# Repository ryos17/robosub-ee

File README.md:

# Stanford RoboSub — Electrical Repo

Electrical subsystem for the Stanford RoboSub AUV. It includes PCB designs (KiCad), firmware, Python tools, and research.

🌐 [stanfordrobosub.org](https://www.stanfordrobosub.org/)

## Repository layout

- **`platformio.ini`** — PlatformIO config for building/flashing the Teensy firmware. `src_dir` points at one sketch folder; change it to pick which firmware gets flashed (see comments in the file).
- **`gen1/`** — First hardware generation: PCBs only. Deprecated; the sub no longer exists.
- **`gen2/`** — Second (current) generation: PCBs and firmware for the audio and Teensy boards.
- **`gen3/`** — Third generation (in progress): ongoing designs of PCBs with Micro Breakout, Battery Boards, Power Distribution.
- **`imported_parts/`** — Shared KiCad libraries: symbols, footprints, 3D models, import script, and the JLC parts order log.
- **`misc/`** — Older and experimental material.
- **`research/`** — Research work (whisper-based intervehicle communication).

## Sub setup (Jetson Orin)

### Fix the system clock

The Jetson has no battery-backed RTC, so after being powered off its clock can be wrong. A wrong date breaks TLS, so Claude Code, `git`, `pip`, etc. fail to connect. Fix it by syncing over the internet:

```bash
timedatectl                      # check: "System clock synchronized" and the date
sudo timedatectl set-ntp true    # sync the time over the internet
sudo systemctl restart systemd-timesyncd
timedatectl                      # the date should now be correct
```

### Connect to eduroam (Stanford)

Replace `SUNETID` and the password with your own (Stanford eduroam uses PEAP / MSCHAPv2 with `sunetid@stanford.edu` as the identity):

```bash
nmcli connection add type wifi ifname wlP1p1s0 con-name eduroam ssid eduroam \
  wifi-sec.key-mgmt wpa-eap 802-1x.eap peap 802-1x.phase2-auth mschapv2 \
  802-1x.identity SUNETID@stanford.edu 802-1x.password 'YOUR_PASSWORD'
nmcli connection up eduroam
```

If an `eduroam` connection already exists, update it instead of adding a new one:

```bash
nmcli connection modify eduroam 802-1x.identity SUNETID@stanford.edu 802-1x.password 'YOUR_PASSWORD'
nmcli connection up eduroam
```

Don't commit your password. Afterwards, run the clock fix above if Claude still can't connect.

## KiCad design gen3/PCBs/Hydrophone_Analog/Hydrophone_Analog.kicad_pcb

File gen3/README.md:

# Gen 3 Submarine (in progress)

The third hardware generation, currently being designed. The proposed system
architecture is shown below; the boards under [`PCBs/`](PCBs/) are the work
toward it. The current working vehicle is still [`gen2/`](../gen2/).

## PCBs

- **`Micro_Breakout/`** — the main breakout board for gen 3, the successor to
  the gen 2 MLU breakout. References the shared parts library in
  [`../../imported_parts`](../../imported_parts).
- **`Battery_Boards/`** — the gen 3 power-management / battery boards, the
  follow-on to the gen 2 `Power_Management` boards (which had heat problems).
  Two design variants:
  - **`Power_ManagementV3_diode/`** — the diode-based design; this is the lead
    design.
  - **`Power_ManagementV3_eli/`** — Eli's alternative design, kept as a backup.
- **`Power_Distribution/`** — the gen 3 power-distribution board (battery →
  rails).
- **`to_order/`** — staging area for boards that are ready to be fabricated
  (currently empty).

## TODO

- Finalize how signals/power route in and out of `Micro_Breakout`, and choose
  the physical dimensions of all the boards.
- Order the PCBs.

_Last updated: 2026-07-20_

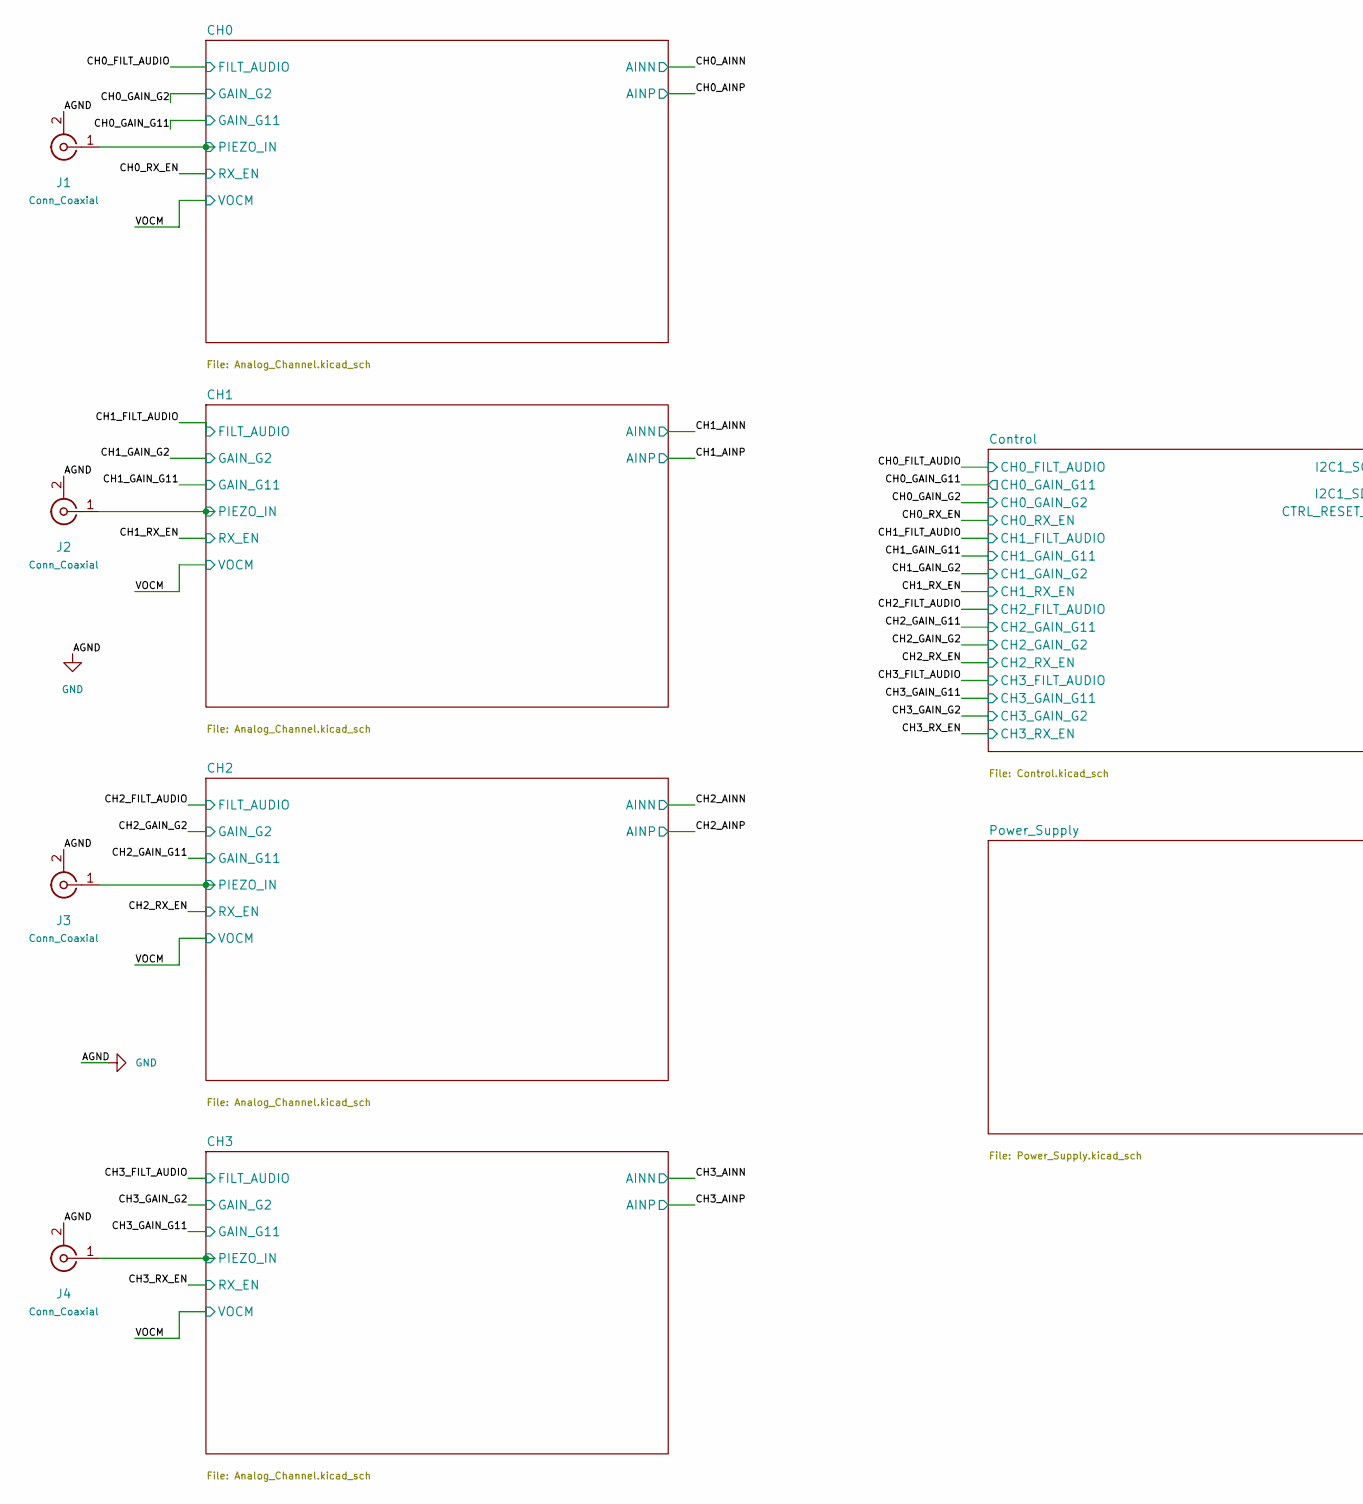
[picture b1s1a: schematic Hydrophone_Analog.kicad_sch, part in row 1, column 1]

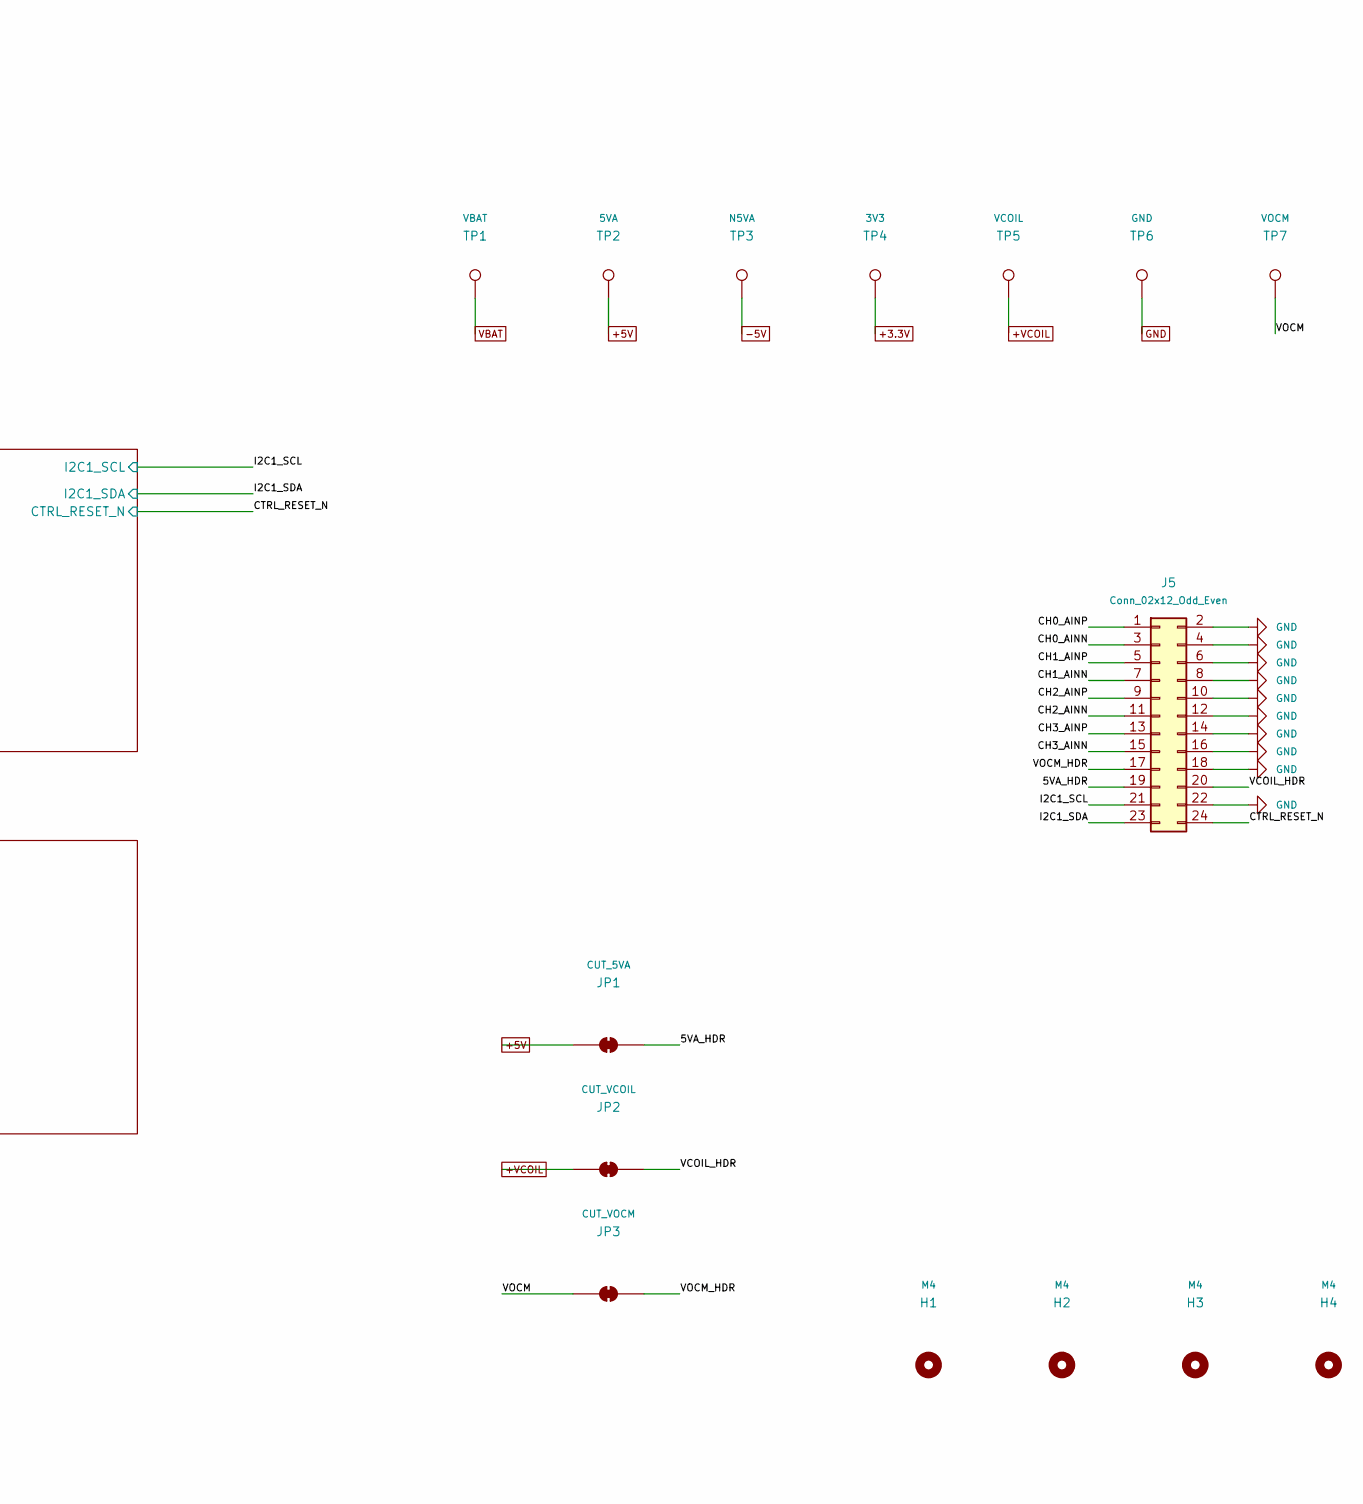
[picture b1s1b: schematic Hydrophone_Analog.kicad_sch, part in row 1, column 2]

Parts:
H1, H2, H3, H4: M4; MountingHole_4.3mm_M4
J1, J2, J3, J4: Conn_Coaxial; PinHeader_1x02_P2.54mm_Vertical
J5: Conn_02x12_Odd_Even; PinHeader_2x12_P2.54mm_Horizontal_BoardEdge
JP1: CUT_5VA; SolderJumper-2_P1.3mm_Bridged_RoundedPad1.0x1.5mm
JP2: CUT_VCOIL; SolderJumper-2_P1.3mm_Bridged_RoundedPad1.0x1.5mm
JP3: CUT_VOCM; SolderJumper-2_P1.3mm_Bridged_RoundedPad1.0x1.5mm
TP1: VBAT; TestPoint_Pad_D1.5mm
TP2: 5VA; TestPoint_Pad_D1.5mm
TP3: N5VA; TestPoint_Pad_D1.5mm
TP4: 3V3; TestPoint_Pad_D1.5mm
TP5: VCOIL; TestPoint_Pad_D1.5mm
TP6: GND; TestPoint_Pad_D1.5mm
TP7: VOCM; TestPoint_Pad_D1.5mm

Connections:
+3.3V: TP4.1; also elsewhere on the board
+5V: JP1.1 (A), TP2.1; also elsewhere on the board
+VCOIL: JP2.1 (A), TP5.1; also elsewhere on the board
-5V: TP3.1; also elsewhere on the board
/5VA_HDR: J5.19, JP1.2 (B)
/CH0/PIEZO_IN: J1.1 (In); also elsewhere on the board
/CH0_AINN: J5.3; also elsewhere on the board
/CH0_AINP: J5.1; also elsewhere on the board
/CH1/PIEZO_IN: J2.1 (In); also elsewhere on the board
/CH1_AINN: J5.7; also elsewhere on the board
/CH1_AINP: J5.5; also elsewhere on the board
/CH2/PIEZO_IN: J3.1 (In); also elsewhere on the board
/CH2_AINN: J5.11; also elsewhere on the board
/CH2_AINP: J5.9; also elsewhere on the board
/CH3/PIEZO_IN: J4.1 (In); also elsewhere on the board
/CH3_AINN: J5.15; also elsewhere on the board
/CH3_AINP: J5.13; also elsewhere on the board
/CTRL_RESET_N: J5.24; also elsewhere on the board
/I2C1_SCL: J5.21; also elsewhere on the board
/I2C1_SDA: J5.23; also elsewhere on the board
/VCOIL_HDR: J5.20, JP2.2 (B)
/VOCM: JP3.1 (A), TP7.1; also elsewhere on the board
/VOCM_HDR: J5.17, JP3.2 (B)
GND: J1.2 (Ext), J2.2 (Ext), J3.2 (Ext), J4.2 (Ext), J5.2, J5.4, J5.6, J5.8, J5.10, J5.12, J5.14, J5.16, J5.18, J5.22, TP6.1; also elsewhere on the board
VBAT: TP1.1; also elsewhere on the board

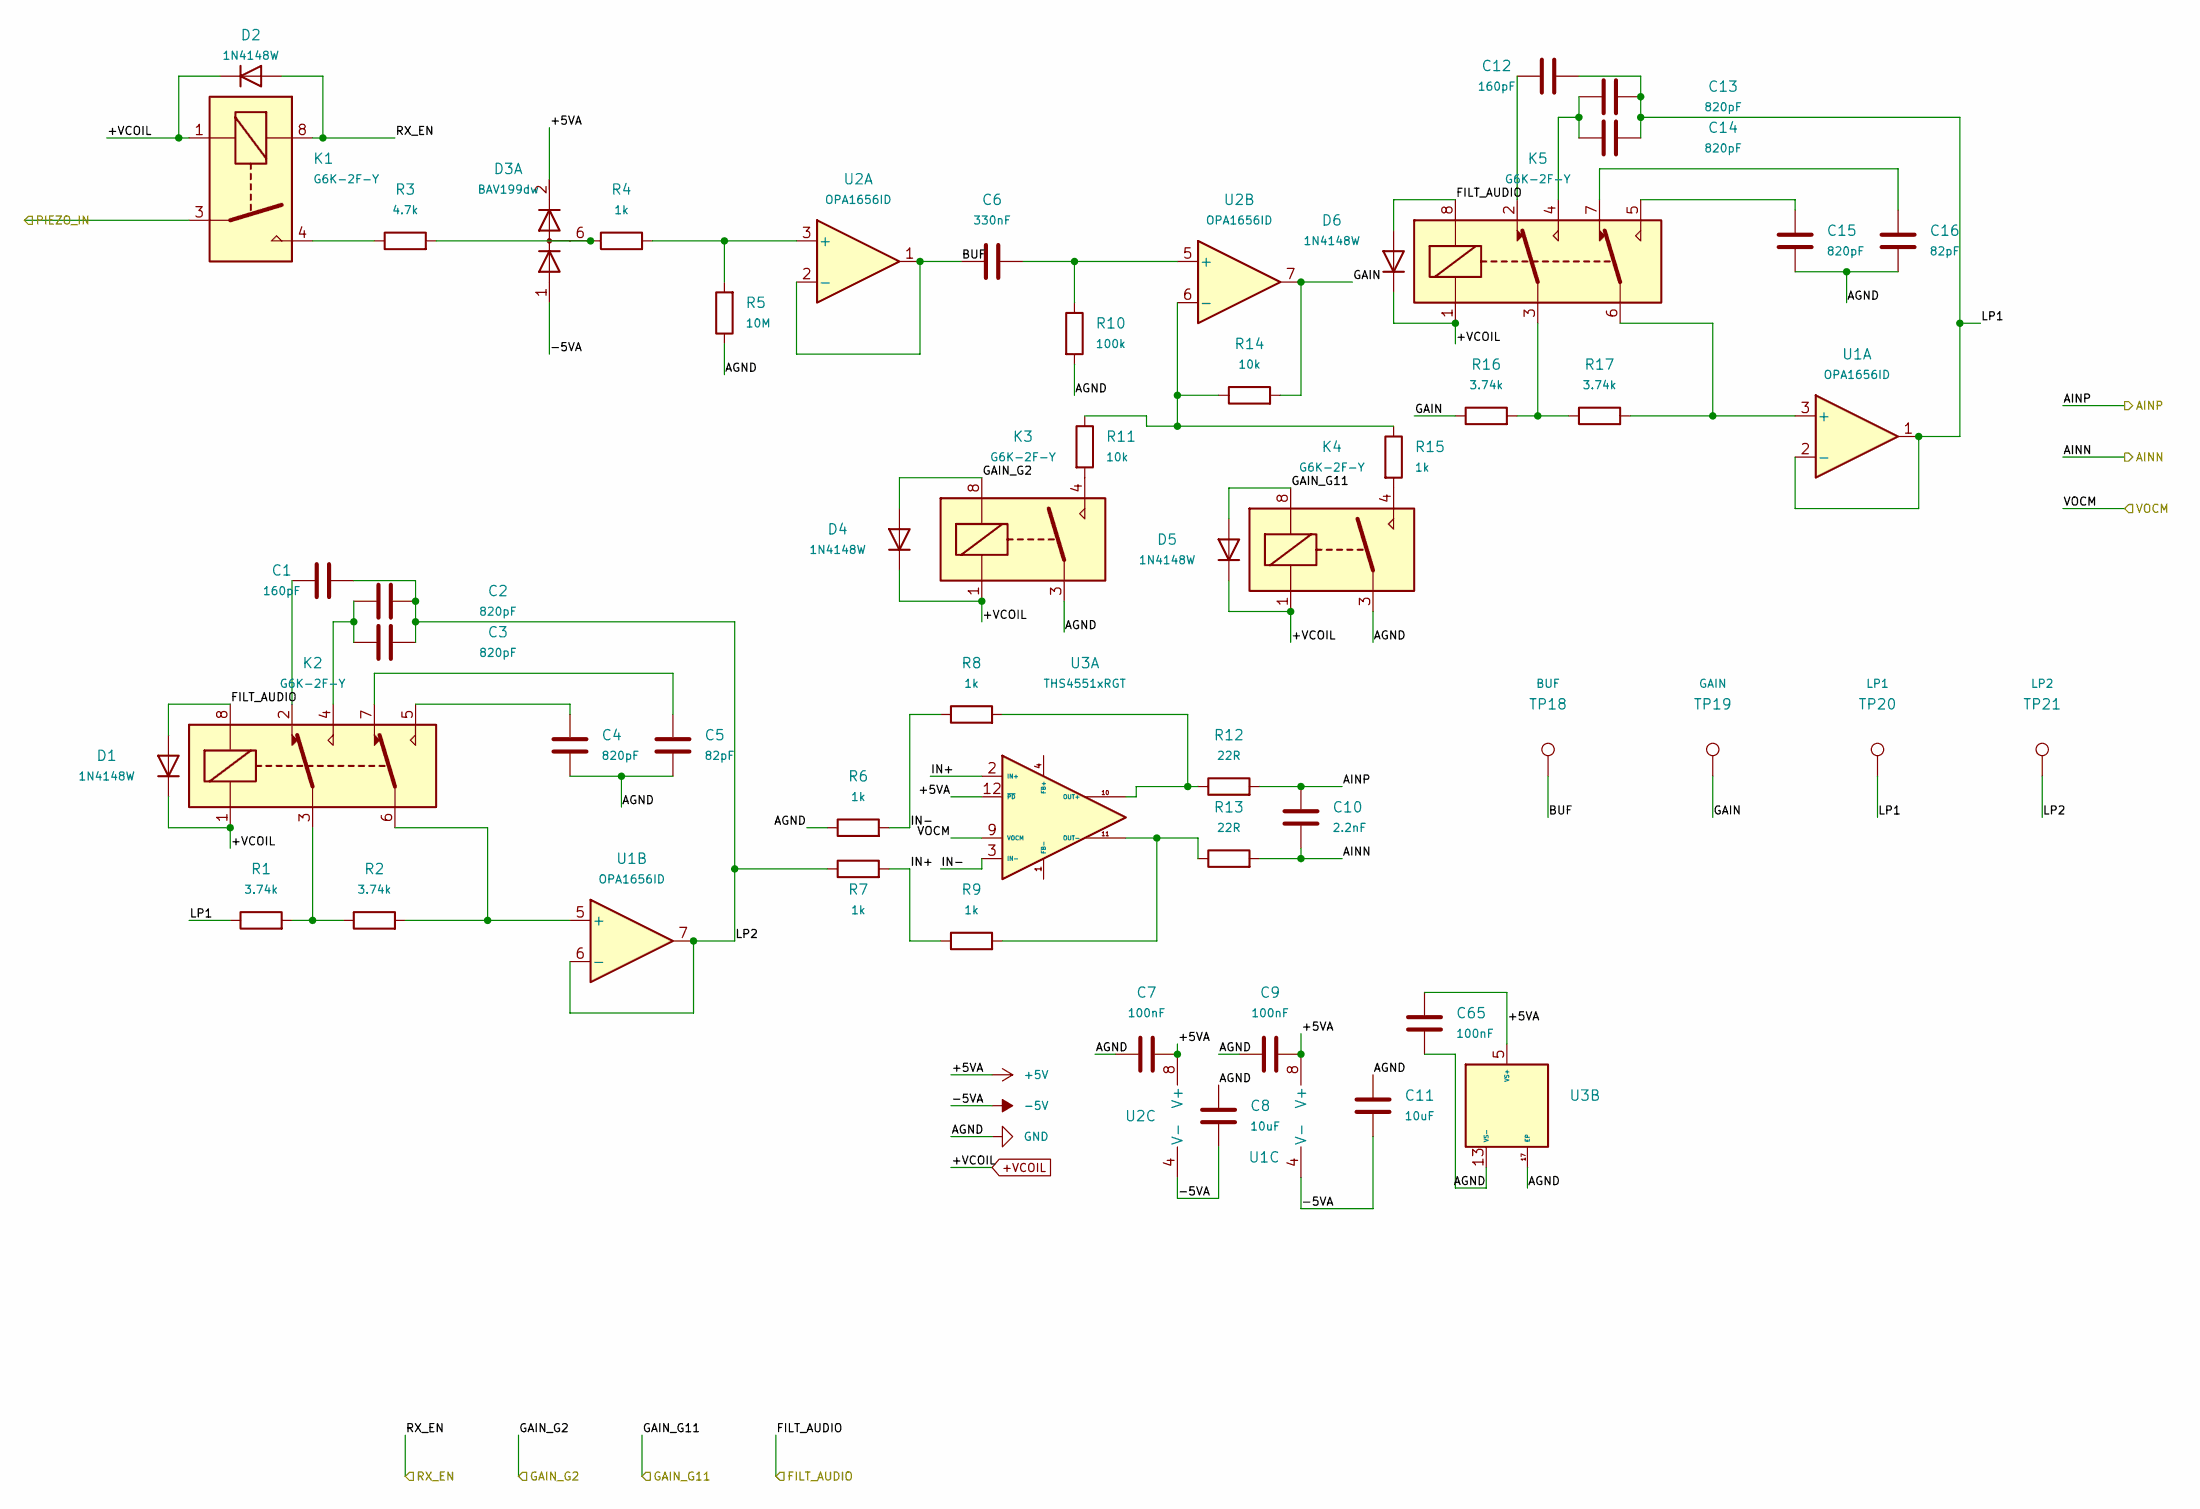
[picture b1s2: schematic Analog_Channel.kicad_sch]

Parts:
C1, C12: 160pF; C_0805_2012Metric
C2, C3, C4, C13, C14, C15: 820pF; C_0805_2012Metric
C5, C16: 82pF; C_0805_2012Metric
C6: 330nF; C_0805_2012Metric
C7, C9, C65: 100nF; C_0805_2012Metric
C8, C11: 10uF; C_1206_3216Metric
C10: 2.2nF; C_0805_2012Metric
D1, D2, D4, D5, D6: 1N4148W; D_SOD-123
D3: BAV199dw; SOT-363_SC-70-6
K1, K2, K3, K4, K5: G6K-2F-Y; Relay_DPDT_Omron_G6K-2F-Y
R1, R2, R16, R17: 3.74k; R_0805_2012Metric
R3: 4.7k; R_0805_2012Metric
R4, R6, R7, R8, R9, R15: 1k; R_0805_2012Metric
R5: 10M; R_0805_2012Metric
R10: 100k; R_0805_2012Metric
R11, R14: 10k; R_0805_2012Metric
R12, R13: 22R; R_0805_2012Metric
TP18: BUF; TestPoint_Pad_D1.0mm
TP19: GAIN; TestPoint_Pad_D1.0mm
TP20: LP1; TestPoint_Pad_D1.0mm
TP21: LP2; TestPoint_Pad_D1.0mm
U1, U2: OPA1656ID; SOIC-8_3.9x4.9mm_P1.27mm
U3: THS4551xRGT; VQFN-16-1EP_3x3mm_P0.5mm_EP1.68x1.68mm

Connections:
+5V: C7.2, C9.2, C65.2, D3.2 (K2), U1.8 (V+), U2.8 (V+), U3.5 (VS+), U3.6 (VS+), U3.7 (VS+), U3.8 (VS+), U3.12 (~PD); also elsewhere on the board
+VCOIL: D1.1 (K), D2.1 (K), D4.1 (K), D5.1 (K), D6.1 (K), K1.1 (A2), K2.1 (A2), K3.1 (A2), K4.1 (A2), K5.1 (A2); also elsewhere on the board
-5V: C8.2, C11.2, D3.1 (A1), U1.4 (V-), U2.4 (V-); also elsewhere on the board
/CH0/BUF: C6.1, TP18.1, U2.1, U2.2 (-)
/CH0/GAIN: R14.2, R16.1, TP19.1, U2.7
/CH0/IN+: R7.2, R9.1, U3.2 (IN+)
/CH0/IN-: R6.2, R8.1, U3.3 (IN-)
/CH0/LP1: C12.2, C13.2, C14.2, R1.1, TP20.1, U1.1, U1.2 (-)
/CH0/LP2: C1.2, C2.2, C3.2, R7.1, TP21.1, U1.6 (-), U1.7
/CH0/PIEZO_IN: K1.3 (13); also elsewhere on the board
/CH0_AINN: C10.2, R13.2; also elsewhere on the board
/CH0_AINP: C10.1, R12.2; also elsewhere on the board
/CH0_FILT_AUDIO: D1.2 (A), D6.2 (A), K2.8 (A1), K5.8 (A1); also elsewhere on the board
/CH0_GAIN_G2: D4.2 (A), K3.8 (A1); also elsewhere on the board
/CH0_GAIN_G11: D5.2 (A), K4.8 (A1); also elsewhere on the board
/CH0_RX_EN: D2.2 (A), K1.8 (A1); also elsewhere on the board
/VOCM: U3.9 (VOCM); also elsewhere on the board
GND: C4.2, C5.2, C7.1, C8.1, C9.1, C11.1, C15.2, C16.2, C65.1, K3.3 (13), K4.3 (13), R5.1, R6.1, R10.2, U3.13 (VS-), U3.14 (VS-), U3.15 (VS-), U3.16 (VS-), U3.17 (EP); also elsewhere on the board
unnamed: D3.6 (K3A4), R3.2, R4.1
unnamed: K1.4 (14), R3.1
unnamed: K2.3 (11), R1.2, R2.1
unnamed: C1.1, K2.2 (12)
unnamed: C2.1, C3.1, K2.4 (14)
unnamed: K2.6 (21), R2.2, U1.5 (+)
unnamed: C5.1, K2.7 (22)
unnamed: C4.1, K2.5 (24)
unnamed: K3.4 (14), R11.2
unnamed: K4.4 (14), R15.2
unnamed: K5.3 (11), R16.2, R17.1
unnamed: C12.1, K5.2 (12)
unnamed: C13.1, C14.1, K5.4 (14)
unnamed: K5.6 (21), R17.2, U1.3 (+)
unnamed: C16.1, K5.7 (22)
unnamed: C15.1, K5.5 (24)
unnamed: R4.2, R5.2, U2.3 (+)
unnamed: C6.2, R10.1, U2.5 (+)
unnamed: R11.1, R14.1, R15.1, U2.6 (-)
unnamed: R8.2, R12.1, U3.10 (OUT+)
unnamed: R9.2, R13.1, U3.11 (OUT-)

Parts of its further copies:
C17, C28, C33, C44, C49, C60: 160pF; C_0805_2012Metric
C18, C19, C20, C29, C30, C31, C34, C35, C36, C45, C46, C47, C50, C51, C52, C61, C62, C63: 820pF; C_0805_2012Metric
C21, C32, C37, C48, C53, C64: 82pF; C_0805_2012Metric
C22, C38, C54: 330nF; C_0805_2012Metric
C23, C25, C39, C41, C55, C57, C66, C67, C68: 100nF; C_0805_2012Metric
C24, C27, C40, C43, C56, C59: 10uF; C_1206_3216Metric
C26, C42, C58: 2.2nF; C_0805_2012Metric
D7, D8, D10, D11, D12, D13, D14, D16, D17, D18, D19, D20, D22, D23, D24: 1N4148W; D_SOD-123
D9, D15, D21: BAV199dw; SOT-363_SC-70-6
K6, K7, K8, K9, K10, K11, K12, K13, K14, K15, K16, K17, K18, K19, K20: G6K-2F-Y; Relay_DPDT_Omron_G6K-2F-Y
R18, R19, R33, R34, R35, R36, R50, R51, R52, R53, R67, R68: 3.74k; R_0805_2012Metric
R20, R37, R54: 4.7k; R_0805_2012Metric
R21, R23, R24, R25, R26, R32, R38, R40, R41, R42, R43, R49, R55, R57, R58, R59, R60, R66: 1k; R_0805_2012Metric
R22, R39, R56: 10M; R_0805_2012Metric
R27, R44, R61: 100k; R_0805_2012Metric
R28, R31, R45, R48, R62, R65: 10k; R_0805_2012Metric
R29, R30, R46, R47, R63, R64: 22R; R_0805_2012Metric
TP10, TP14, TP22: BUF; TestPoint_Pad_D1.0mm
TP11, TP15, TP23: GAIN; TestPoint_Pad_D1.0mm
TP12, TP16, TP24: LP1; TestPoint_Pad_D1.0mm
TP13, TP17, TP25: LP2; TestPoint_Pad_D1.0mm
U4, U5, U10, U11, U16, U17: OPA1656ID; SOIC-8_3.9x4.9mm_P1.27mm
U6, U12, U18: THS4551xRGT; VQFN-16-1EP_3x3mm_P0.5mm_EP1.68x1.68mm

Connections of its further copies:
+5V: C23.2, C25.2, C39.2, C41.2, C55.2, C57.2, C66.2, C67.2, C68.2, D9.2 (K2), D15.2 (K2), D21.2 (K2), U4.8 (V+), U5.8 (V+), U6.5 (VS+), U6.6 (VS+), U6.7 (VS+), U6.8 (VS+), U6.12 (~PD), U10.8 (V+), U11.8 (V+), U12.5 (VS+), U12.6 (VS+), U12.7 (VS+), U12.8 (VS+), U12.12 (~PD), U16.8 (V+), U17.8 (V+), U18.5 (VS+), U18.6 (VS+), U18.7 (VS+), U18.8 (VS+), U18.12 (~PD); also elsewhere on the board
+VCOIL: D7.1 (K), D8.1 (K), D10.1 (K), D11.1 (K), D12.1 (K), D13.1 (K), D14.1 (K), D16.1 (K), D17.1 (K), D18.1 (K), D19.1 (K), D20.1 (K), D22.1 (K), D23.1 (K), D24.1 (K), K6.1 (A2), K7.1 (A2), K8.1 (A2), K9.1 (A2), K10.1 (A2), K11.1 (A2), K12.1 (A2), K13.1 (A2), K14.1 (A2), K15.1 (A2), K16.1 (A2), K17.1 (A2), K18.1 (A2), K19.1 (A2), K20.1 (A2); also elsewhere on the board
-5V: C24.2, C27.2, C40.2, C43.2, C56.2, C59.2, D9.1 (A1), D15.1 (A1), D21.1 (A1), U4.4 (V-), U5.4 (V-), U10.4 (V-), U11.4 (V-), U16.4 (V-), U17.4 (V-); also elsewhere on the board
/CH1/BUF: C22.1, TP10.1, U5.1, U5.2 (-)
/CH1/GAIN: R31.2, R33.1, TP11.1, U5.7
/CH1/IN+: R24.2, R26.1, U6.2 (IN+)
/CH1/IN-: R23.2, R25.1, U6.3 (IN-)
/CH1/LP1: C28.2, C29.2, C30.2, R18.1, TP12.1, U4.1, U4.2 (-)
/CH1/LP2: C17.2, C18.2, C19.2, R24.1, TP13.1, U4.6 (-), U4.7
/CH1/PIEZO_IN: K6.3 (13); also elsewhere on the board
/CH1_AINN: C26.2, R30.2; also elsewhere on the board
/CH1_AINP: C26.1, R29.2; also elsewhere on the board
/CH1_FILT_AUDIO: D7.2 (A), D12.2 (A), K7.8 (A1), K10.8 (A1); also elsewhere on the board
/CH1_GAIN_G2: D10.2 (A), K8.8 (A1); also elsewhere on the board
/CH1_GAIN_G11: D11.2 (A), K9.8 (A1); also elsewhere on the board
/CH1_RX_EN: D8.2 (A), K6.8 (A1); also elsewhere on the board
/CH2/BUF: C38.1, TP14.1, U10.1, U10.2 (-)
/CH2/GAIN: R48.2, R50.1, TP15.1, U10.7
/CH2/IN+: R41.2, R43.1, U12.2 (IN+)
/CH2/IN-: R40.2, R42.1, U12.3 (IN-)
/CH2/LP1: C44.2, C45.2, C46.2, R35.1, TP16.1, U11.1, U11.2 (-)
/CH2/LP2: C33.2, C34.2, C35.2, R41.1, TP17.1, U11.6 (-), U11.7
/CH2/PIEZO_IN: K11.3 (13); also elsewhere on the board
/CH2_AINN: C42.2, R47.2; also elsewhere on the board
/CH2_AINP: C42.1, R46.2; also elsewhere on the board
/CH2_FILT_AUDIO: D13.2 (A), D18.2 (A), K12.8 (A1), K15.8 (A1); also elsewhere on the board
/CH2_GAIN_G2: D16.2 (A), K13.8 (A1); also elsewhere on the board
/CH2_GAIN_G11: D17.2 (A), K14.8 (A1); also elsewhere on the board
/CH2_RX_EN: D14.2 (A), K11.8 (A1); also elsewhere on the board
/CH3/BUF: C54.1, TP22.1, U16.1, U16.2 (-)
/CH3/GAIN: R65.2, R67.1, TP23.1, U16.7
/CH3/IN+: R58.2, R60.1, U18.2 (IN+)
/CH3/IN-: R57.2, R59.1, U18.3 (IN-)
/CH3/LP1: C60.2, C61.2, C62.2, R52.1, TP24.1, U17.1, U17.2 (-)
/CH3/LP2: C49.2, C50.2, C51.2, R58.1, TP25.1, U17.6 (-), U17.7
/CH3/PIEZO_IN: K16.3 (13); also elsewhere on the board
/CH3_AINN: C58.2, R64.2; also elsewhere on the board
/CH3_AINP: C58.1, R63.2; also elsewhere on the board
/CH3_FILT_AUDIO: D19.2 (A), D24.2 (A), K17.8 (A1), K20.8 (A1); also elsewhere on the board
/CH3_GAIN_G2: D22.2 (A), K18.8 (A1); also elsewhere on the board
/CH3_GAIN_G11: D23.2 (A), K19.8 (A1); also elsewhere on the board
/CH3_RX_EN: D20.2 (A), K16.8 (A1); also elsewhere on the board
/VOCM: U6.9 (VOCM), U12.9 (VOCM), U18.9 (VOCM); also elsewhere on the board
GND: C20.2, C21.2, C23.1, C24.1, C25.1, C27.1, C31.2, C32.2, C36.2, C37.2, C39.1, C40.1, C41.1, C43.1, C47.2, C48.2, C52.2, C53.2, C55.1, C56.1, C57.1, C59.1, C63.2, C64.2, C66.1, C67.1, C68.1, K8.3 (13), K9.3 (13), K13.3 (13), K14.3 (13), K18.3 (13), K19.3 (13), R22.1, R23.1, R27.2, R39.1, R40.1, R44.2, R56.1, R57.1, R61.2, U6.13 (VS-), U6.14 (VS-), U6.15 (VS-), U6.16 (VS-), U6.17 (EP), U12.13 (VS-), U12.14 (VS-), U12.15 (VS-), U12.16 (VS-), U12.17 (EP), U18.13 (VS-), U18.14 (VS-), U18.15 (VS-), U18.16 (VS-), U18.17 (EP); also elsewhere on the board
unnamed: D9.6 (K3A4), R20.2, R21.1
unnamed: D15.6 (K3A4), R37.2, R38.1
unnamed: D21.6 (K3A4), R54.2, R55.1
unnamed: K6.4 (14), R20.1
unnamed: K7.3 (11), R18.2, R19.1
unnamed: C17.1, K7.2 (12)
unnamed: C18.1, C19.1, K7.4 (14)
unnamed: K7.6 (21), R19.2, U4.5 (+)
unnamed: C21.1, K7.7 (22)
unnamed: C20.1, K7.5 (24)
unnamed: K8.4 (14), R28.2
unnamed: K9.4 (14), R32.2
unnamed: K10.3 (11), R33.2, R34.1
unnamed: C28.1, K10.2 (12)
unnamed: C29.1, C30.1, K10.4 (14)
unnamed: K10.6 (21), R34.2, U4.3 (+)
unnamed: C32.1, K10.7 (22)
unnamed: C31.1, K10.5 (24)
unnamed: K11.4 (14), R37.1
unnamed: K12.3 (11), R35.2, R36.1
unnamed: C33.1, K12.2 (12)
unnamed: C34.1, C35.1, K12.4 (14)
unnamed: K12.6 (21), R36.2, U11.5 (+)
unnamed: C37.1, K12.7 (22)
unnamed: C36.1, K12.5 (24)
unnamed: K13.4 (14), R45.2
unnamed: K14.4 (14), R49.2
unnamed: K15.3 (11), R50.2, R51.1
unnamed: C44.1, K15.2 (12)
unnamed: C45.1, C46.1, K15.4 (14)
unnamed: K15.6 (21), R51.2, U11.3 (+)
unnamed: C48.1, K15.7 (22)
unnamed: C47.1, K15.5 (24)
unnamed: K16.4 (14), R54.1
unnamed: K17.3 (11), R52.2, R53.1
unnamed: C49.1, K17.2 (12)
unnamed: C50.1, C51.1, K17.4 (14)
unnamed: K17.6 (21), R53.2, U17.5 (+)
unnamed: C53.1, K17.7 (22)
unnamed: C52.1, K17.5 (24)
unnamed: K18.4 (14), R62.2
unnamed: K19.4 (14), R66.2
unnamed: K20.3 (11), R67.2, R68.1
unnamed: C60.1, K20.2 (12)
unnamed: C61.1, C62.1, K20.4 (14)
unnamed: K20.6 (21), R68.2, U17.3 (+)
unnamed: C64.1, K20.7 (22)
unnamed: C63.1, K20.5 (24)
unnamed: R21.2, R22.2, U5.3 (+)
unnamed: C22.2, R27.1, U5.5 (+)
unnamed: R28.1, R31.1, R32.1, U5.6 (-)
unnamed: R25.2, R29.1, U6.10 (OUT+)
unnamed: R26.2, R30.1, U6.11 (OUT-)
unnamed: R38.2, R39.2, U10.3 (+)
unnamed: C38.2, R44.1, U10.5 (+)
unnamed: R45.1, R48.1, R49.1, U10.6 (-)
unnamed: R42.2, R46.1, U12.10 (OUT+)
unnamed: R43.2, R47.1, U12.11 (OUT-)
unnamed: R55.2, R56.2, U16.3 (+)
unnamed: C54.2, R61.1, U16.5 (+)
unnamed: R62.1, R65.1, R66.1, U16.6 (-)
unnamed: R59.2, R63.1, U18.10 (OUT+)
unnamed: R60.2, R64.1, U18.11 (OUT-)

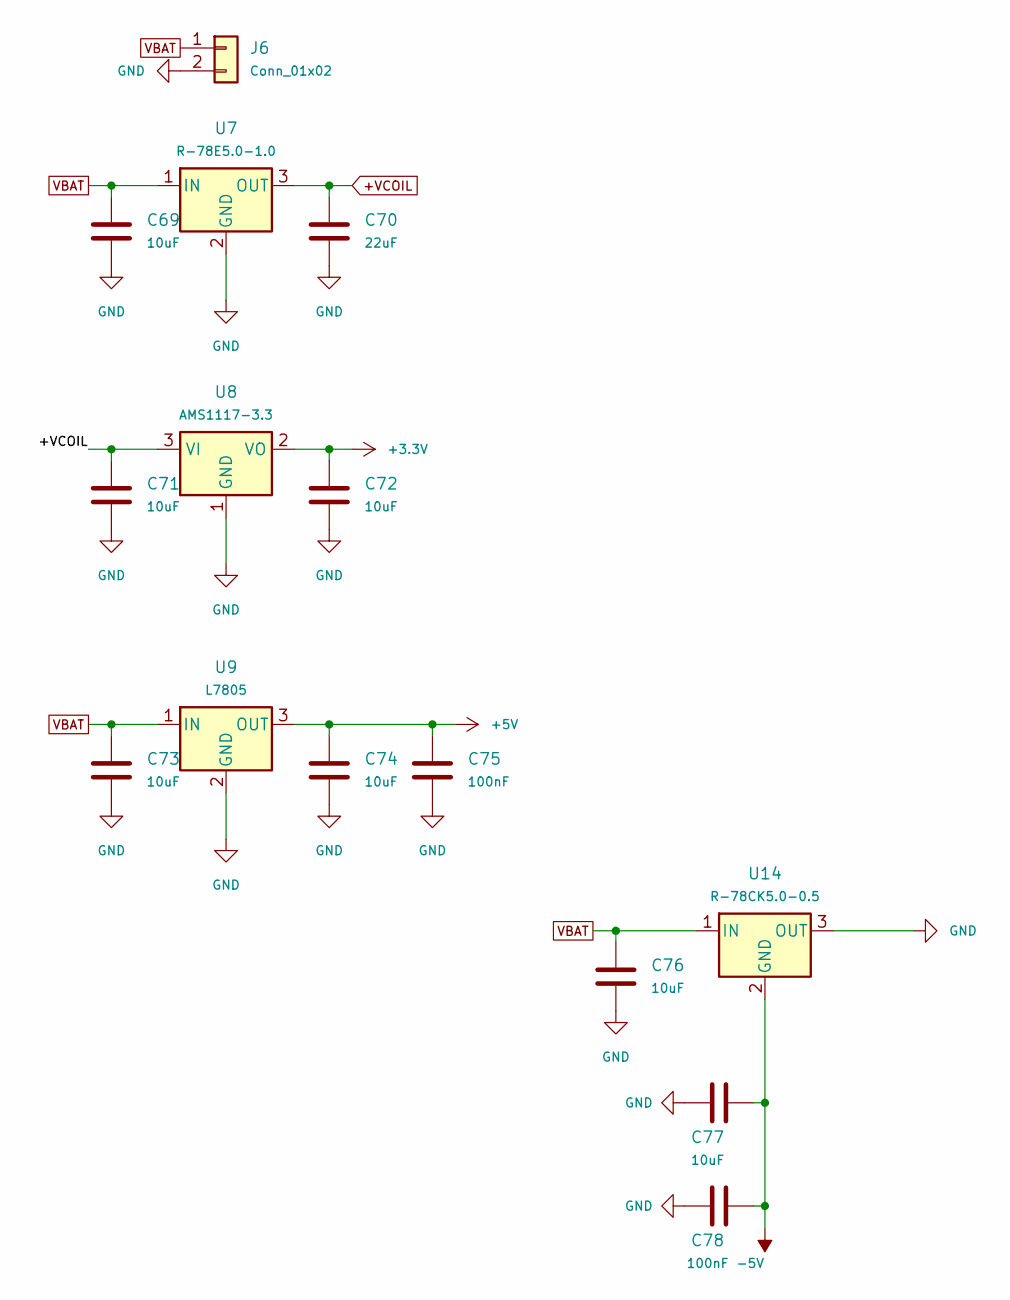
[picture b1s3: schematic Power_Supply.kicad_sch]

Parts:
C69, C71, C72, C73, C74, C76, C77: 10uF; C_1206_3216Metric
C70: 22uF; C_1206_3216Metric
C75, C78: 100nF; C_0805_2012Metric
J6: Conn_01x02; TerminalBlock_Phoenix_MKDS-1,5-2-5.08_1x02_P5.08mm_Horizont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
U7: R-78E5.0-1.0; Converter_DCDC_RECOM_R-78E-0.5_THT
U8: AMS1117-3.3; SOT-223-3_TabPin2
U9: L7805; TO-252-2
U14: R-78CK5.0-0.5; Converter_DCDC_RECOM_R-78E-0.5_THT

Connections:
+3.3V: C72.1, U8.2 (VO); also elsewhere on the board
+5V: C74.1, C75.1, U9.3 (OUT); also elsewhere on the board
+VCOIL: C70.1, C71.1, U7.3 (OUT), U8.3 (VI); also elsewhere on the board
-5V: C77.1, C78.1, U14.2 (GND); also elsewhere on the board
GND: C69.2, C70.2, C71.2, C72.2, C73.2, C74.2, C75.2, C76.2, C77.2, C78.2, J6.2, U7.2 (GND), U8.1 (GND), U9.2 (GND), U14.3 (OUT); also elsewhere on the board
VBAT: C69.1, C73.1, C76.1, J6.1, U7.1 (IN), U9.1 (IN), U14.1 (IN); also elsewhere on the board

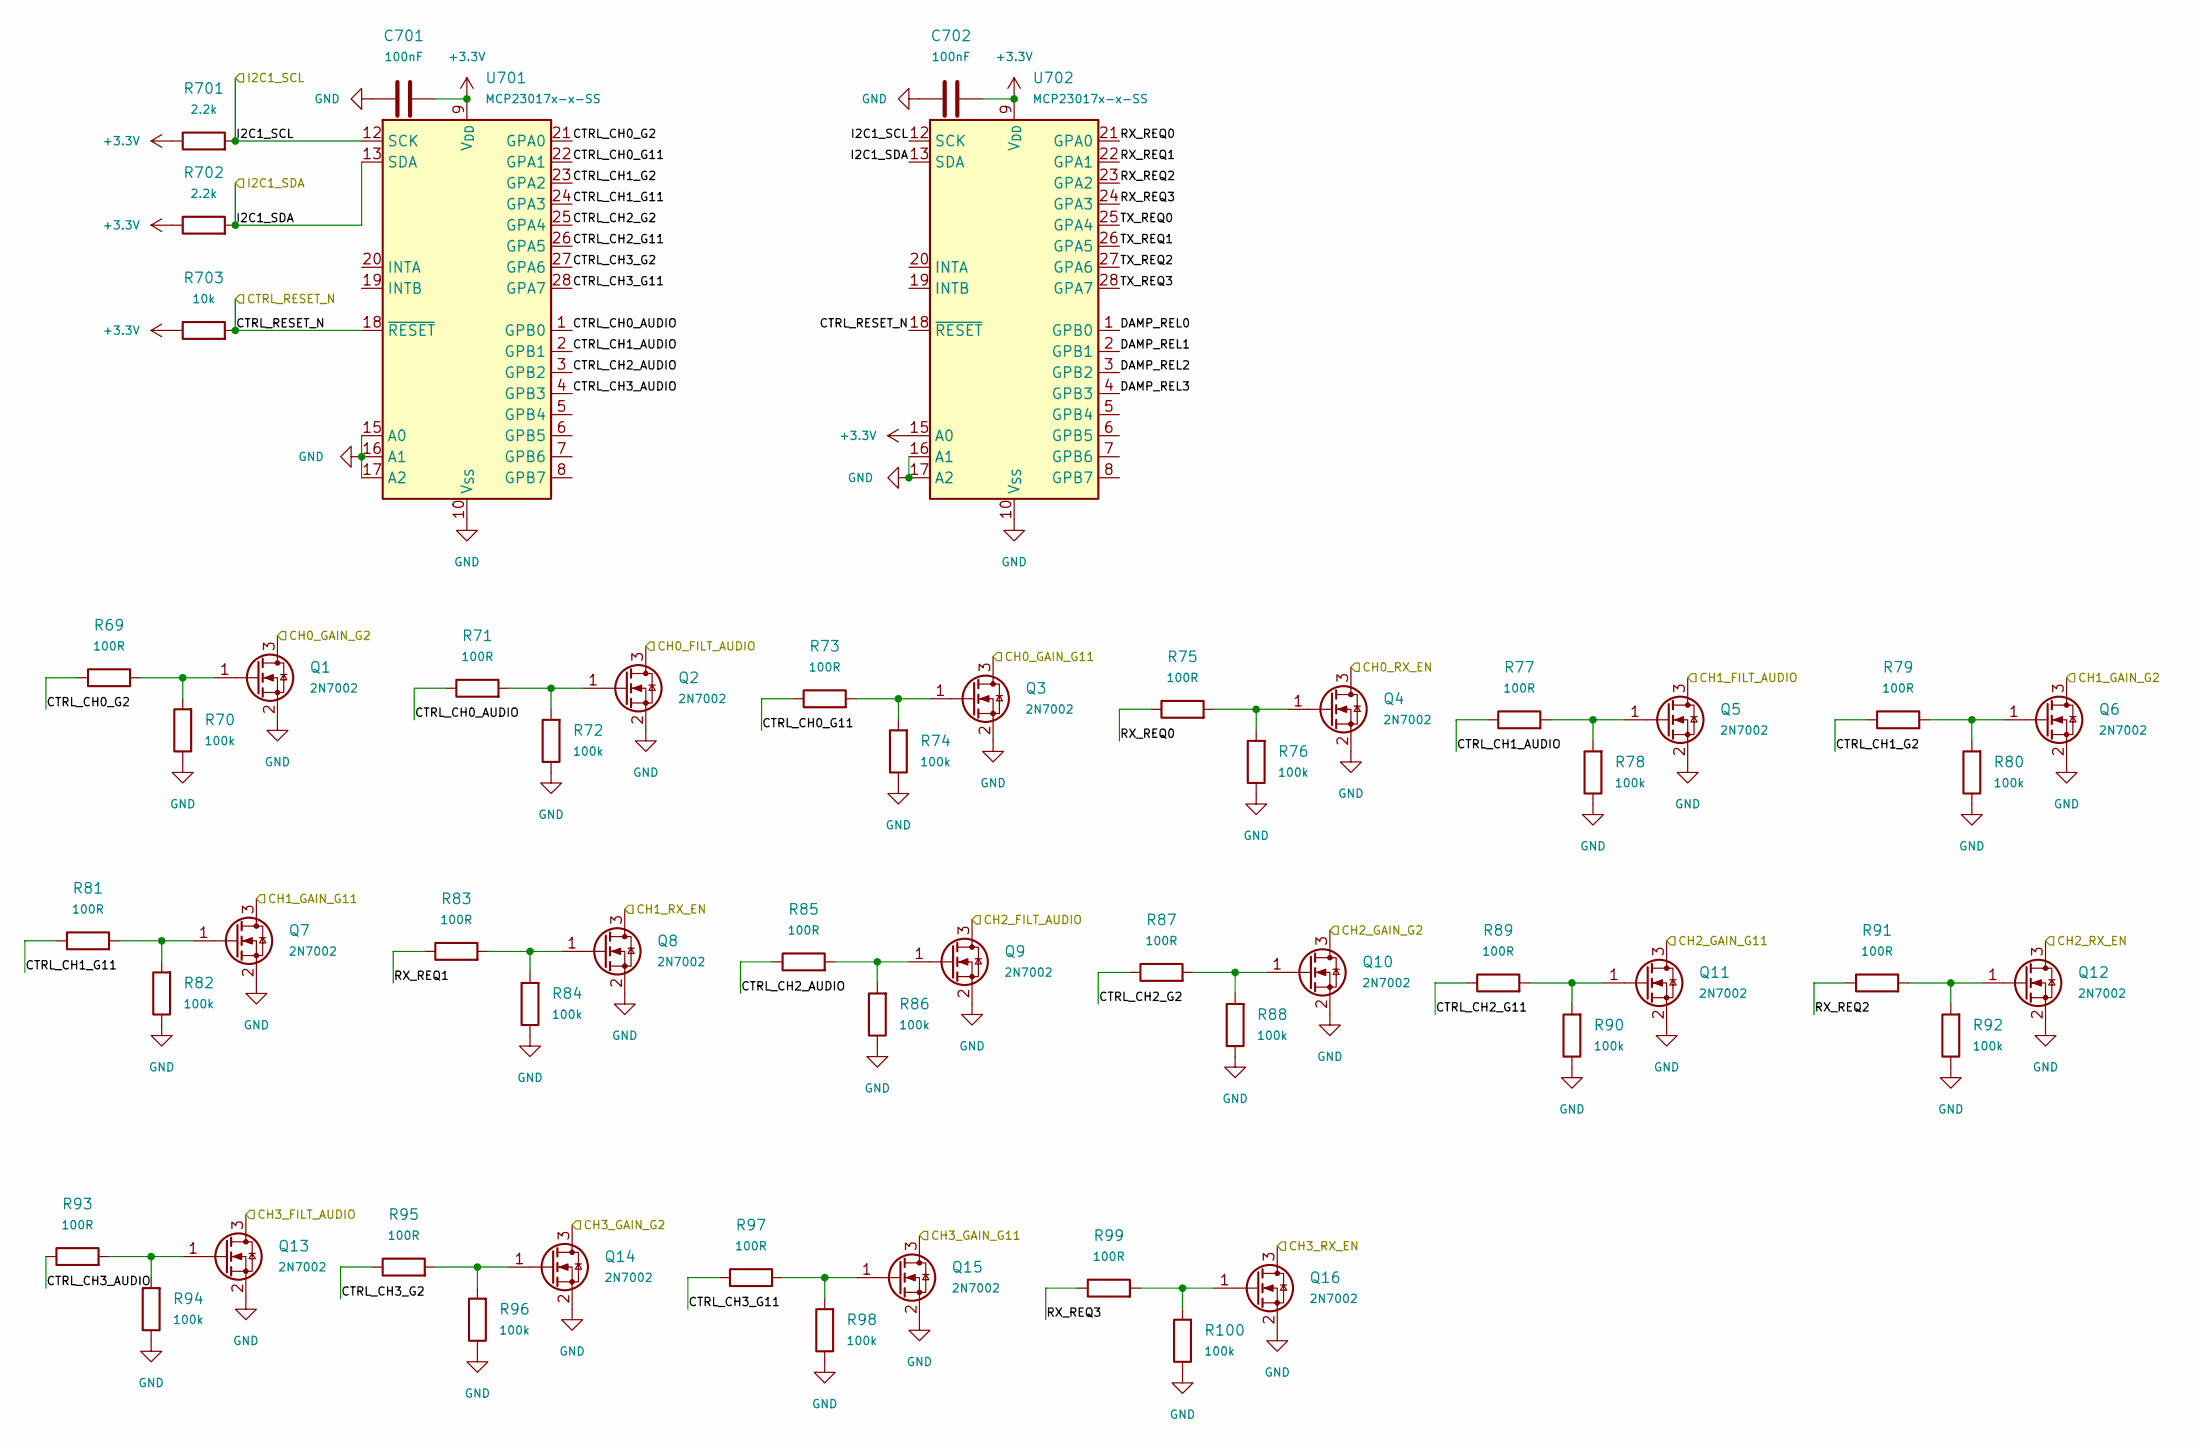
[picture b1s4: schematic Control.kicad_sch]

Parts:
C701, C702: 100nF; C_0805_2012Metric
Q1, Q2, Q3, Q4, Q5, Q6, Q7, Q8, Q9, Q10, Q11, Q12, Q13, Q14, Q15, Q16: 2N7002; SOT-23
R69, R71, R73, R75, R77, R79, R81, R83, R85, R87, R89, R91, R93, R95, R97, R99: 100R; R_0805_2012Metric
R70, R72, R74, R76, R78, R80, R82, R84, R86, R88, R90, R92, R94, R96, R98, R100: 100k; R_0805_2012Metric
R701, R702: 2.2k; R_0805_2012Metric
R703: 10k; R_0805_2012Metric
U701, U702: MCP23017x-x-SS; SSOP-28_5.3x10.2mm_P0.65mm

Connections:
+3.3V: C701.2, C702.2, R701.1, R702.1, R703.1, U701.9 (V_{DD}), U702.9 (V_{DD}), U702.15 (A0); also elsewhere on the board
/CH0_FILT_AUDIO: Q2.3 (D); also elsewhere on the board
/CH0_GAIN_G2: Q1.3 (D); also elsewhere on the board
/CH0_GAIN_G11: Q3.3 (D); also elsewhere on the board
/CH0_RX_EN: Q4.3 (D); also elsewhere on the board
/CH1_FILT_AUDIO: Q5.3 (D); also elsewhere on the board
/CH1_GAIN_G2: Q6.3 (D); also elsewhere on the board
/CH1_GAIN_G11: Q7.3 (D); also elsewhere on the board
/CH1_RX_EN: Q8.3 (D); also elsewhere on the board
/CH2_FILT_AUDIO: Q9.3 (D); also elsewhere on the board
/CH2_GAIN_G2: Q10.3 (D); also elsewhere on the board
/CH2_GAIN_G11: Q11.3 (D); also elsewhere on the board
/CH2_RX_EN: Q12.3 (D); also elsewhere on the board
/CH3_FILT_AUDIO: Q13.3 (D); also elsewhere on the board
/CH3_GAIN_G2: Q14.3 (D); also elsewhere on the board
/CH3_GAIN_G11: Q15.3 (D); also elsewhere on the board
/CH3_RX_EN: Q16.3 (D); also elsewhere on the board
/CTRL_RESET_N: R703.2, U701.18 (~RESET), U702.18 (~RESET); also elsewhere on the board
/Control/CTRL_CH0_AUDIO: R71.1, U701.1 (GPB0)
/Control/CTRL_CH0_G2: R69.1, U701.21 (GPA0)
/Control/CTRL_CH0_G11: R73.1, U701.22 (GPA1)
/Control/CTRL_CH1_AUDIO: R77.1, U701.2 (GPB1)
/Control/CTRL_CH1_G2: R79.1, U701.23 (GPA2)
/Control/CTRL_CH1_G11: R81.1, U701.24 (GPA3)
/Control/CTRL_CH2_AUDIO: R85.1, U701.3 (GPB2)
/Control/CTRL_CH2_G2: R87.1, U701.25 (GPA4)
/Control/CTRL_CH2_G11: R89.1, U701.26 (GPA5)
/Control/CTRL_CH3_AUDIO: R93.1, U701.4 (GPB3)
/Control/CTRL_CH3_G2: R95.1, U701.27 (GPA6)
/Control/CTRL_CH3_G11: R97.1, U701.28 (GPA7)
/Control/DAMP_REL0: U702.1 (GPB0)
/Control/DAMP_REL1: U702.2 (GPB1)
/Control/DAMP_REL2: U702.3 (GPB2)
/Control/DAMP_REL3: U702.4 (GPB3)
/Control/RX_REQ0: R75.1, U702.21 (GPA0)
/Control/RX_REQ1: R83.1, U702.22 (GPA1)
/Control/RX_REQ2: R91.1, U702.23 (GPA2)
/Control/RX_REQ3: R99.1, U702.24 (GPA3)
/Control/TX_REQ0: U702.25 (GPA4)
/Control/TX_REQ1: U702.26 (GPA5)
/Control/TX_REQ2: U702.27 (GPA6)
/Control/TX_REQ3: U702.28 (GPA7)
/I2C1_SCL: R701.2, U701.12 (SCK), U702.12 (SCK); also elsewhere on the board
/I2C1_SDA: R702.2, U701.13 (SDA), U702.13 (SDA); also elsewhere on the board
GND: C701.1, C702.1, Q1.2 (S), Q2.2 (S), Q3.2 (S), Q4.2 (S), Q5.2 (S), Q6.2 (S), Q7.2 (S), Q8.2 (S), Q9.2 (S), Q10.2 (S), Q11.2 (S), Q12.2 (S), Q13.2 (S), Q14.2 (S), Q15.2 (S), Q16.2 (S), R70.1, R72.1, R74.1, R76.1, R78.1, R80.1, R82.1, R84.1, R86.1, R88.1, R90.1, R92.1, R94.1, R96.1, R98.1, R100.1, U701.10 (V_{SS}), U701.15 (A0), U701.16 (A1), U701.17 (A2), U702.10 (V_{SS}), U702.16 (A1), U702.17 (A2); also elsewhere on the board
unnamed: Q1.1 (G), R69.2, R70.2
unnamed: Q2.1 (G), R71.2, R72.2
unnamed: Q3.1 (G), R73.2, R74.2
unnamed: Q4.1 (G), R75.2, R76.2
unnamed: Q5.1 (G), R77.2, R78.2
unnamed: Q6.1 (G), R79.2, R80.2
unnamed: Q7.1 (G), R81.2, R82.2
unnamed: Q8.1 (G), R83.2, R84.2
unnamed: Q9.1 (G), R85.2, R86.2
unnamed: Q10.1 (G), R87.2, R88.2
unnamed: Q11.1 (G), R89.2, R90.2
unnamed: Q12.1 (G), R91.2, R92.2
unnamed: Q13.1 (G), R93.2, R94.2
unnamed: Q14.1 (G), R95.2, R96.2
unnamed: Q15.1 (G), R97.2, R98.2
unnamed: Q16.1 (G), R99.2, R100.2
